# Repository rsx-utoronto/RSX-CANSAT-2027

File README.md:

# RSX-CANSAT-2027

This repository contains all files created by the Aerial Team of Robotics for Space eXploration (RSX) at the University of Toronto, supporting our entry in the 2027 CanSat Competition.

## Competition Team Members:
| Name | Role |
|---|---|
| Yechun(Vincent) Jia | Software Team Lead |
| Yulin Lin | Electrical Team Lead |
| Nathan Xia | Mechanical Team Co-Lead |
| Jingshu Zhu | Mechanical Team Co-Lead |
| Parth Bhasin | Software Team Junior Lead |
| Remi Zhang | Software Team Member |
| More... |  |

## ESP32 firmware: one PlatformIO project

Open the repository root in VS Code with **PlatformIO IDE** and **C/C++**
installed. The root PlatformIO configuration is the entry point for all three
boot-only firmware environments:

| Environment | Role | Source directory, relative to the repository root |
|---|---|---|
| `ground_station` (default) | Ground-station ESP32 | `software/firmware/ground/src` |
| `pq` | PocketQube ESP32 | `software/firmware/PQ/src` |
| `container` | Container ESP32 | `software/firmware/container/src` |

All environments use the pinned `platformio/espressif32@8.0.0` platform,
Arduino-ESP32 3.3.12, and the `esp32dev` profile (4 MB flash, no PSRAM).
This covers our ESP32-DevKitC V4 boards with ESP32-WROOM-32E or
ESP32-WROOM-32UE modules. The UE variant uses an external antenna connector;
connect the appropriate antenna before future radio testing.

The role builds share `software/firmware_lib` through a local symlink dependency;
editing that library does not require copying it into each project. Role-specific
source filters and include paths keep the three application entry points separate.
The existing library manifest and its dependency declarations are retained.

### Build and choose an environment

Run commands from the repository root. In VS Code, use the PlatformIO terminal
and **Project Tasks** to select the desired environment. Outside that terminal,
`pio` may be available as `~/.platformio/penv/bin/pio` on macOS/Linux or through
`platformio` on your PATH. The first build needs network access to install the
pinned platform, framework, toolchain, and library dependencies.

```sh
# Default environment: ground_station only.
pio run

# Build an individual role.
pio run -e ground_station
pio run -e pq
pio run -e container

# Build all three roles explicitly; this does not upload anything.
pio run -e ground_station -e pq -e container
```

### Upload and monitor: explicit board selection

**Uploading replaces the selected board's existing application.** Label the board
with its role first, identify its port with `pio device list`, and replace `PORT`
below with that exact port (for example, a `/dev/cu.*` port on macOS or `COM4` on
Windows). Ports are deliberately not committed to the configuration.

```sh
pio device list

# Use exactly one role per upload; choose the command matching the labelled board.
pio run -e ground_station -t upload --upload-port PORT
pio run -e pq -t upload --upload-port PORT
pio run -e container -t upload --upload-port PORT

# Open the matching serial port; all roles use 115200 baud.
pio device monitor --port PORT --baud 115200
```

After opening the monitor, press **EN/reset** to see the one-time application
banner. For a ground-station board it has this form (the MAC is illustrative):

```text
ROLE=GROUND_STATION
MAC=AA:BB:CC:DD:EE:FF
MODE=BOOT_ONLY
```

The other role labels are `PQ` and `CONTAINER`. If reading the station MAC fails,
the middle line is `MAC=UNAVAILABLE (error=ERROR_CODE)`; startup still completes.
The MAC is read through `esp_read_mac(..., ESP_MAC_WIFI_STA)` without starting
Wi-Fi. Startup has only a bounded 250 ms settling delay; each idle loop yields
for 10 ms. There is no terminal-connection wait or recurring application output.
ESP32 ROM/bootloader messages may appear before this application banner.

### Inactive hardware boundary and preserved prototypes

These are **boot-only skeletons**, not deployed mission or communication firmware.
They do not initialize Wi-Fi/ESP-NOW, access sensors, drive actuators, or connect
to the desktop GUI. No peer MACs, radio channels, or actuator pins are configured.
The unresolved protocol, sensor, and mission interfaces are intentionally not used.

The original radio-bridge prototype remains unchanged under
`ground_station/gs_radio_firmware`; it is not part of any root-project build.
Its old empty PlatformIO configuration and the two empty per-flight-role
configurations have been removed. Existing experimental PlatformIO projects,
the shared library's historical standalone configuration, and both Python GUI
copies are unchanged. Incomplete `software/common` telemetry code is also excluded.
The old GUI/bridge baud-rate and framing mismatches remain unresolved.

### Host checks and physical acceptance

```sh
python3 -m unittest discover -s software/tests -p 'test_boot_skeleton.py' -v
```

These checks compile the real startup helper and all three real entry points
against small host fakes using a C++17 compiler (`c++`, or the `CXX` executable).
They verify role isolation, boot banners, MAC-read errors, and yielding idle loops.
They are not hardware tests. Physical acceptance requires an explicitly selected
board/port, a successful upload, and observing that board's role and actual MAC
at 115200 baud. Building or running host checks never flashes a board.

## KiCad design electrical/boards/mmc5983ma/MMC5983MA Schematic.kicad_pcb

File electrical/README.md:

# Electrical

| Folder | Contents |
|---|---|
| `lib/` | The Aerial KiCad library: symbols, footprints (`RSX_Aerial.pretty/`), 3D models (`3d/`) |
| `boards/` | One folder per board, each holding its KiCad project |
| `blocks/` | Reusable schematic sheets, one circuit each (INA236 current sensor, IMU) |
| `test/` | Sensor and radio tests (PlatformIO projects) |
| `docs/` | Documentation |

## 1. Install KiCad 10 first

Everyone uses KiCad 10. Install it from [kicad.org/download](https://www.kicad.org/download/) **before opening any file in this repo**.

- The boards here are already in KiCad 10 format, and KiCad 9 can't open them.

## 2. Use the Aerial library

We now have our own library in `lib/`. Every part comes from the Aerial library or from KiCad's built-in libraries. **Don't use the old RSX library any more.**

**First, remove the old RSX library:** in **Preferences → Manage Symbol Libraries** and **Manage Footprint Libraries**, delete every `rsx_*` entry. Keep KiCad's own libraries.

**Then load the Aerial library in one of two ways:**

### Option A: add it to your global libraries (recommended)

1. **Preferences → Manage Symbol Libraries** → **Global Libraries** → click the folder icon, go to `electrical/lib/` in your copy of this repo, and select all eight `RSX_Aerial*.kicad_sym` files. 
2. **Preferences → Manage Footprint Libraries** → **Global Libraries** → add `RSX_Aerial.pretty` and `RSX_Aerial_Graphics.pretty`.

You should end up with KiCad's libraries plus the `RSX_Aerial…` entries.

### Option B: use the board's library tables (no setup)

If a board's folder has a `sym-lib-table` and `fp-lib-table` (copied in when the board was made, see [Starting a new board](#starting-a-new-board)), opening its `.kicad_pro` loads the Aerial library automatically, with nothing to set up in KiCad.

However, use option A if you edit blocks(.sch) and doesn't have .pro open.

## 3. Pull before you start

Run `git pull` every time before you open KiCad. The library changes whenever someone adds a part. On an old copy you'll be missing their parts, and your push can clash with their changes.

## Opening a board or block

- **Board:** open the `.kicad_pro` in `boards/<board-name>/`.
- **Block:** `blocks/` isn't a KiCad project. Open the `.kicad_sch` directly in the Schematic Editor (**File → Open**). This needs option A.

## Starting a new board

1. Create the KiCad project directly in `boards/<board-name>/`, not in a subfolder.
2. Copy `lib/templates/sym-lib-table` and `lib/templates/fp-lib-table` into that folder, next to the `.kicad_pro`.

Do this even if you use option A, so the board also works for people using option B. 

## Need a part that isn't in the library?

1. Find the part on Digi-Key and download its KiCad files from the product page (look for **EDA Models**), or from SnapEDA.
2. Send the files and the Digi-Key link to @persfi in the team chat. They will add it to the library and tell you when it's pushed.
3. `git pull`, then use the part.

**Don't change an existing part.** Add to the library only, never change it.

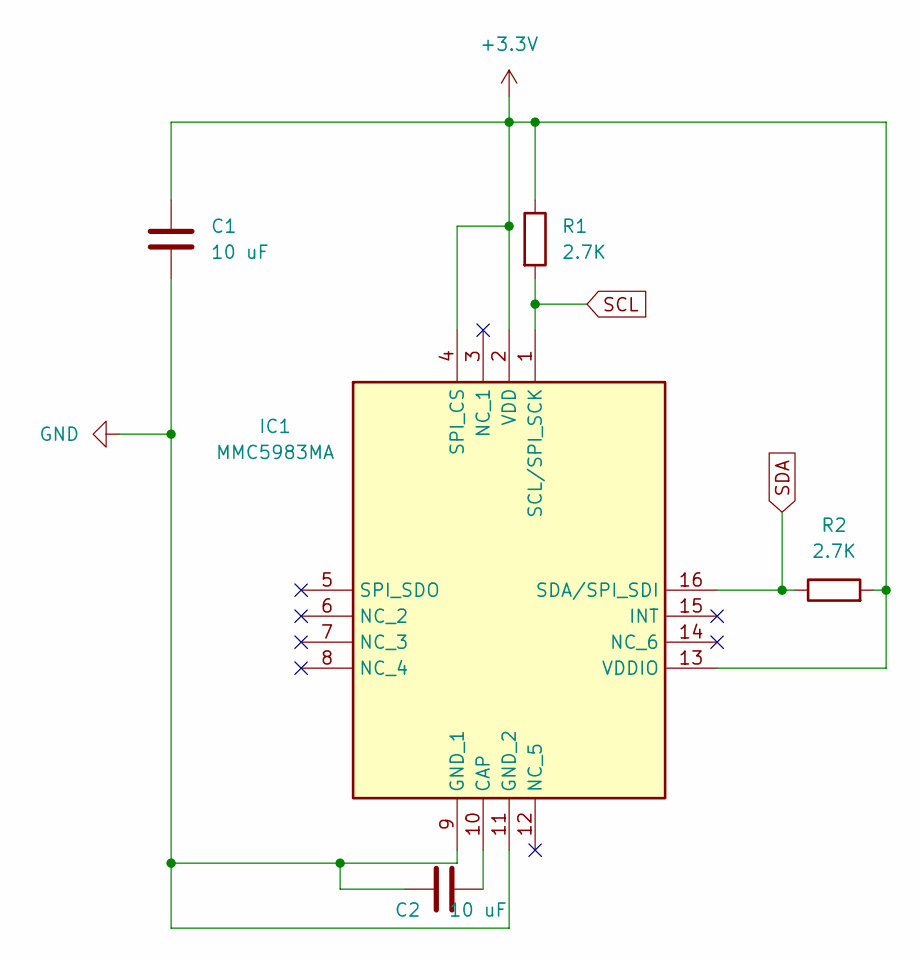
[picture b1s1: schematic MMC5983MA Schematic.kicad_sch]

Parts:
C1, C2: 10 uF; C_0805_2012Metric; MPN GRM21BR61H106KE43L
IC1: MMC5983MA; Manufacturer_Part_Number MMC5983MA; Mouser Part Number 438-MMC5983MA
R1, R2: 2.7K; R_0603_1608Metric; MPN ERA-3AEB302V

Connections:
+3.3V: C1.1, IC1.2 (VDD), IC1.4 (SPI_CS), IC1.13 (VDDIO), R1.1, R2.2
GND: C1.2, C2.1, IC1.9 (GND_1), IC1.11 (GND_2)
unnamed: C2.2, IC1.10 (CAP)
SCL: IC1.1 (SCL/SPI_SCK), R1.2
SDA: IC1.16 (SDA/SPI_SDI), R2.1

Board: 2 copper layers, 5 parts (0 on the bottom side), 5 nets, no tracks yet.

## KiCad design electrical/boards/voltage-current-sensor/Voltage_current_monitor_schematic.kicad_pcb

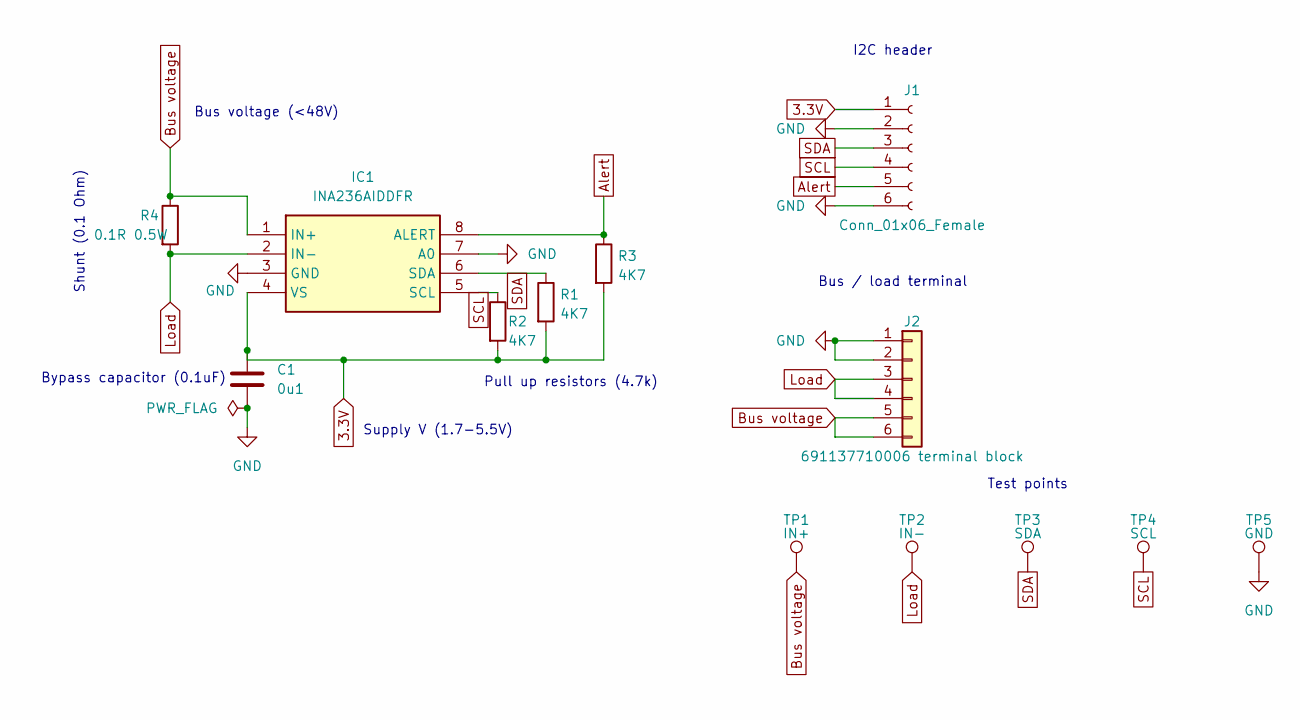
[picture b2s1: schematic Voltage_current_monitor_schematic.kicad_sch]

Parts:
C1: 0u1; C_0603_1608Metric; MPN C1608X7R1H104K080AA
IC1: INA236AIDDFR; SOP65P280X110-8N; Manufacturer_Part_Number INA236AIDDFR; Mouser Part Number 595-INA236AIDDFR
J1: Conn_01x06_Female; PinSocket_1x06_P2.54mm_Vertical; MPN PPTC061LFBN-RC
J2: 691137710006 terminal block; 691137710006; Manufacturer_Part_Number 691137710006; Mouser Part Number 710-691137710006
R1, R2, R3: 4K7; R_0603_1608Metric; MPN RMCF0603FT4K70
R4: 0.1R 0.5W; R_1206_3216Metric; MPN CSR1206FTR100
TP1: IN+; TestPoint_Loop_D2.50mm_Drill1.0mm
TP2: IN-; TestPoint_Loop_D2.50mm_Drill1.0mm
TP3: SDA; TestPoint_Loop_D2.50mm_Drill1.0mm
TP4: SCL; TestPoint_Loop_D2.50mm_Drill1.0mm
TP5: GND; TestPoint_Loop_D2.50mm_Drill1.0mm

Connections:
3.3V: C1.1, IC1.4 (VS), J1.1, R1.2, R2.2, R3.2
Alert: IC1.8 (ALERT), J1.5, R3.1
Bus voltage: IC1.1 (IN+), J2.5, J2.6, R4.1, TP1.1 (1_1)
GND: C1.2, IC1.3 (GND), IC1.7 (A0), J1.2, J1.6, J2.1, J2.2, TP5.1 (1_1)
Load: IC1.2 (IN-), J2.3, J2.4, R4.2, TP2.1 (1_1)
SCL: IC1.5 (SCL), J1.4, R2.1, TP4.1 (1_1)
SDA: IC1.6 (SDA), J1.3, R1.1, TP3.1 (1_1)

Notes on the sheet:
Supply V (1.7-5.5V)
Bypass capacitor (0.1uF)
I2C header
Test points
Shunt (0.1 Ohm)
Bus / load terminal
Pull up resistors (4.7k)
Bus voltage (<48V)

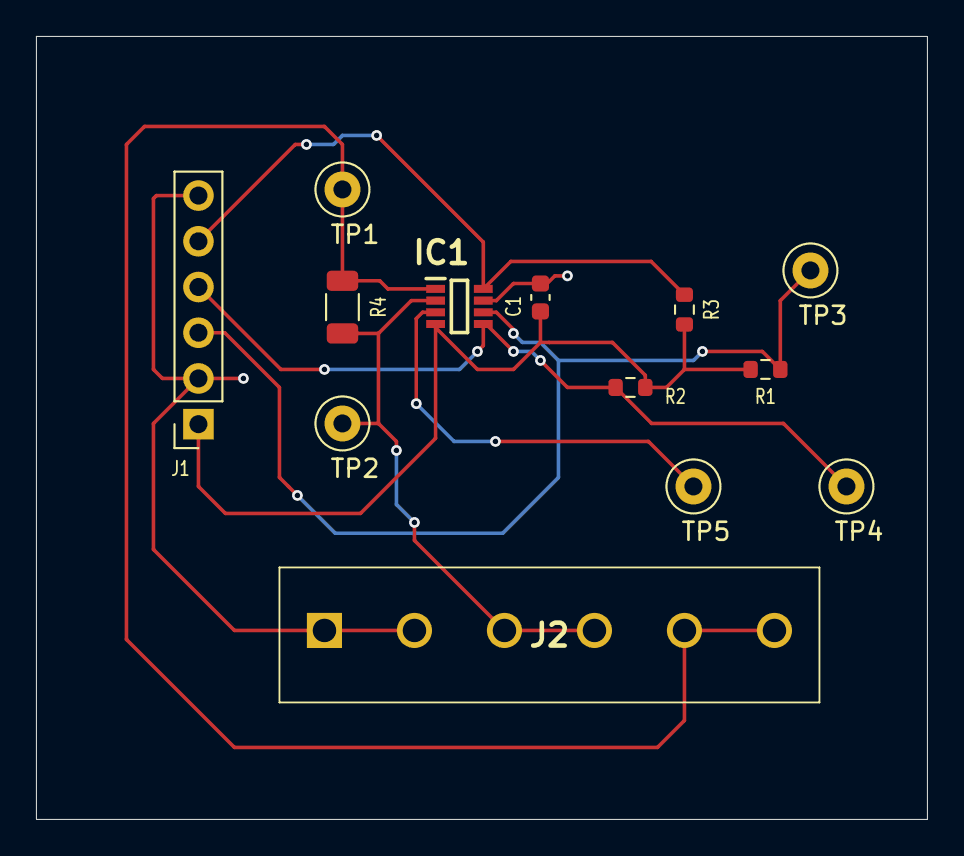
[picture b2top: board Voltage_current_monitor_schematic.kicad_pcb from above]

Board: 2 copper layers, 49.5 x 43.5 mm, 13 parts (0 on the bottom side), 7 nets.
